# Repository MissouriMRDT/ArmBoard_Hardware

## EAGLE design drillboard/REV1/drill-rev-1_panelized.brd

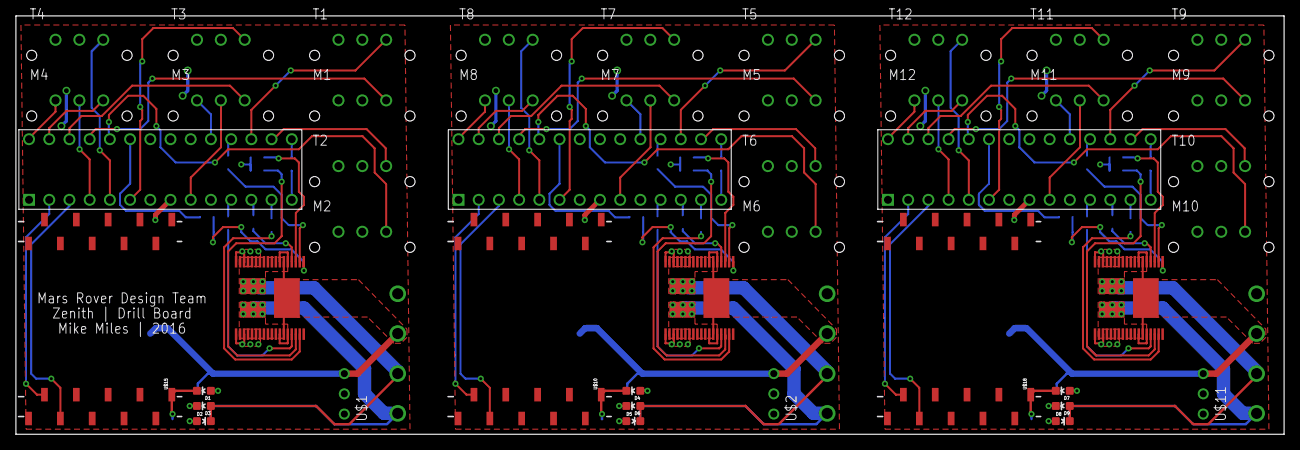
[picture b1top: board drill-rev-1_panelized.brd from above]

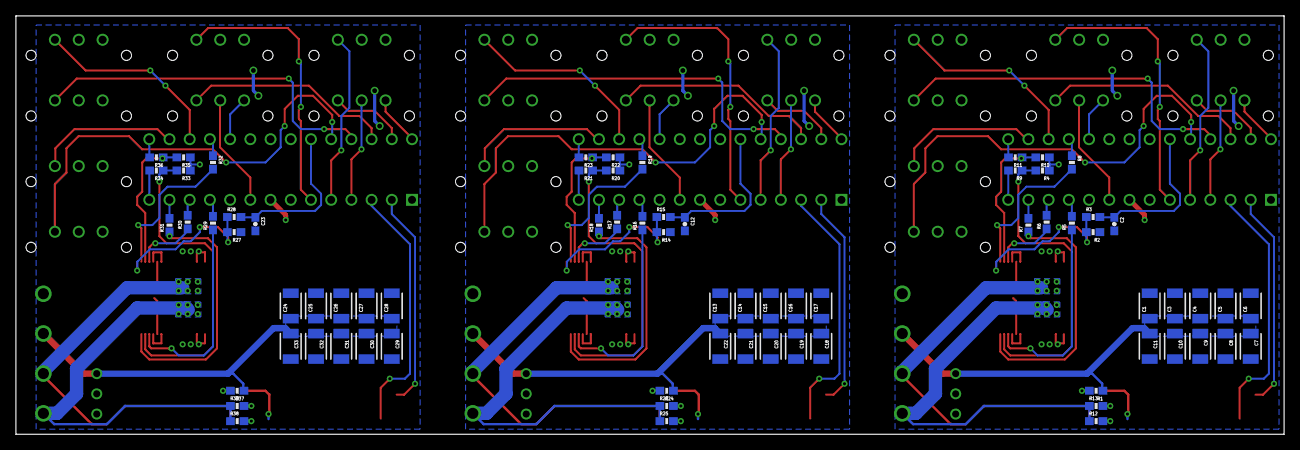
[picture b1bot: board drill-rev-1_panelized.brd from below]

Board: 2 copper layers, 159.4 x 52.6 mm, 123 parts (72 on the bottom side), 108 nets.

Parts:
C1, C3, C4, C5, C6, C7, C8, C9, C10, C11, C13, C14, C15, C16, C17, C18, C19, C20, C21, C22, C24, C25, C26, C27, C28, C29, C30, C31, C32, C33: 47uf; 1210
C2, C12, C23: 33nF; 0603-CAP
D1, D2, D4, D5, D7, D8: red; LED-0603
D3, D6, D9: green; LED-0603
M1, M2, M3, M4, M5, M6, M7, M8, M9, M10, M11, M12: M03VERT; MOLEX0436500328
R1, R5, R6, R7, R9, R11, R12, R13, R16, R17, R18, R21, R23, R24, R25, R26, R29, R30, R31, R34, R36, R37, R38, R39: 1K; 0603-RES
R2, R14, R27: 1.5K; 0603-RES
R3, R15, R28: 10K; 0603-RES
R4, R10, R20, R22, R33, R35: 3K3; 0603-RES
R8, R19, R32: 10k; 0603-RES
T1, T2, T3, T4, T5, T6, T7, T8, T9, T10, T11, T12: M03VERT; MOLEX0436500328
U$1, U$2, U$11: Q_OKI-78SR; OKI-78SR_HORIZ
U$3, U$4, U$5, U$7, U$12, U$14: TE_2POS-5MM_SCREW_TERM
U$6, U$8, U$16: VNH5XXX_HBRIDGEVNH5050A; POWERSSO-36_TP
U$9, U$13, U$17: DIP_SKT_ATMEGA
U$10, U$15, U$18: XBEE_802.15.4SMD; XBEE_802.15.4_SMD

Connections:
+3V1: M5.P$2, M6.P$2, R20.1, R22.1, T5.P$2, T6.P$2, T7.P$2, T8.P$2, U$2.3, U$9.P$7, U$9.P$20, U$9.P$21, U$10.1, U$10.14
+3V2: M9.P$2, M10.P$2, R33.1, R35.1, T9.P$2, T10.P$2, T11.P$2, T12.P$2, U$11.3, U$17.P$7, U$17.P$20, U$17.P$21, U$18.1, U$18.14
+3V3: M1.P$2, M2.P$2, R4.1, R10.1, T1.P$2, T2.P$2, T3.P$2, T4.P$2, U$1.3, U$13.P$7, U$13.P$20, U$13.P$21, U$15.1, U$15.14
+12V: C1.1, C3.1, C4.1, C5.1, C6.1, C7.1, C8.1, C9.1, C10.1, C11.1, R1.1, U$1.1, U$5.P$1, U$6.P$13, U$6.P$24, U$6.SLUG1
+12V1: C13.1, C14.1, C15.1, C16.1, C17.1, C18.1, C19.1, C20.1, C21.1, C22.1, R24.1, U$2.1, U$7.P$1, U$8.P$13, U$8.P$24, U$8.SLUG1
+12V2: C24.1, C25.1, C26.1, C27.1, C28.1, C29.1, C30.1, C31.1, C32.1, C33.1, R37.1, U$11.1, U$14.P$1, U$16.P$13, U$16.P$24, U$16.SLUG1
CS: C2.1, R3.2, U$13.P$23
CS1: C12.1, R15.2, U$9.P$23
CS2: C23.1, R28.2, U$17.P$23
CS_DIS: R8.1, U$13.P$18
CS_DIS1: R19.1, U$9.P$18
CS_DIS2: R32.1, U$17.P$18
D1: M3.P$3, U$13.P$19
D2: M3.P$2, U$13.P$9
D3: M4.P$3, U$13.P$28
D4: M4.P$2, U$13.P$4
D5: M7.P$3, U$9.P$19
D6: M7.P$2, U$9.P$9
D7: M8.P$3, U$9.P$28
D8: M8.P$2, U$9.P$4
D9: M11.P$3, U$17.P$19
D10: M11.P$2, U$17.P$9
D11: M12.P$3, U$17.P$28
D12: M12.P$2, U$17.P$4
ENA: R9.2, U$13.P$14
ENA1: R21.2, U$9.P$14
ENA2: R34.2, U$17.P$14
ENB: R11.2, U$13.P$15
ENB1: R23.2, U$9.P$15
ENB2: R36.2, U$17.P$15
GND: C1.2, C2.2, C3.2, C4.2, C5.2, C6.2, C7.2, C8.2, C9.2, C10.2, C11.2, D1.C, M1.P$3, M2.P$3, R2.1, T1.P$3, T2.P$3, T3.P$3, T4.P$3, U$1.2, U$5.P$2, U$6.P$1, U$6.P$3, U$6.P$4, U$6.P$5, U$6.P$6, U$6.P$7, U$6.P$30, U$6.P$31, U$6.P$32, U$6.P$33, U$6.P$34, U$6.P$36, U$13.P$8, U$13.P$22, U$15.10
GND1: C12.2, C13.2, C14.2, C15.2, C16.2, C17.2, C18.2, C19.2, C20.2, C21.2, C22.2, D4.C, M5.P$3, M6.P$3, R14.1, T5.P$3, T6.P$3, T7.P$3, T8.P$3, U$2.2, U$7.P$2, U$8.P$1, U$8.P$3, U$8.P$4, U$8.P$5, U$8.P$6, U$8.P$7, U$8.P$30, U$8.P$31, U$8.P$32, U$8.P$33, U$8.P$34, U$8.P$36, U$9.P$8, U$9.P$22, U$10.10
GND2: C23.2, C24.2, C25.2, C26.2, C27.2, C28.2, C29.2, C30.2, C31.2, C32.2, C33.2, D7.C, M9.P$3, M10.P$3, R27.1, T9.P$3, T10.P$3, T11.P$3, T12.P$3, U$11.2, U$14.P$2, U$16.P$1, U$16.P$3, U$16.P$4, U$16.P$5, U$16.P$6, U$16.P$7, U$16.P$30, U$16.P$31, U$16.P$32, U$16.P$33, U$16.P$34, U$16.P$36, U$17.P$8, U$17.P$22, U$18.10
INA: R5.2, U$13.P$11
INA1: R16.2, U$9.P$11
INA2: R29.2, U$17.P$11
INB: R6.2, U$13.P$12
INB1: R17.2, U$9.P$12
INB2: R30.2, U$17.P$12
MOIST_1: M1.P$1, U$13.P$25
MOIST_2: M2.P$1, U$13.P$24
MOIST_3: M3.P$1, U$13.P$26
MOIST_4: M4.P$1, U$13.P$27
MOIST_5: M5.P$1, U$9.P$25
MOIST_6: M6.P$1, U$9.P$24
MOIST_7: M7.P$1, U$9.P$26
MOIST_8: M8.P$1, U$9.P$27
MOIST_9: M9.P$1, U$17.P$25
MOIST_10: M10.P$1, U$17.P$24
MOIST_11: M11.P$1, U$17.P$26
MOIST_12: M12.P$1, U$17.P$27
unnamed: R20.2, R21.1, U$8.P$16
unnamed: R4.2, R9.1, U$6.P$16
unnamed: R2.2, R3.1, U$6.P$19
unnamed: D1.A, R1.2
unnamed: D2.A, R12.2
unnamed: R22.2, R23.1, U$8.P$21
unnamed: R10.2, R11.1, U$6.P$21
unnamed: R5.1, U$6.P$15
unnamed: R6.1, U$6.P$22
unnamed: R7.1, U$6.P$17
unnamed: R8.2, U$6.P$20
unnamed: D3.C, R13.2
unnamed: R14.2, R15.1, U$8.P$19
unnamed: R16.1, U$8.P$15
unnamed: R17.1, U$8.P$22
unnamed: R18.1, U$8.P$17
unnamed: R19.2, U$8.P$20
unnamed: D4.A, R24.2
unnamed: D5.A, R25.2
unnamed: D6.C, R26.2
unnamed: R33.2, R34.1, U$16.P$16
unnamed: R35.2, R36.1, U$16.P$21
unnamed: R27.2, R28.1, U$16.P$19
unnamed: R29.1, U$16.P$15
unnamed: R30.1, U$16.P$22
unnamed: R31.1, U$16.P$17
unnamed: R32.2, U$16.P$20
unnamed: D7.A, R37.2
unnamed: D8.A, R38.2
unnamed: D9.C, R39.2
OUTA: R12.1, R13.1, U$3.P$1, U$6.P$2, U$6.P$8, U$6.P$9, U$6.P$10, U$6.P$11, U$6.P$12, U$6.P$14, U$6.SLUG2
OUTA1: R25.1, R26.1, U$4.P$1, U$8.P$2, U$8.P$8, U$8.P$9, U$8.P$10, U$8.P$11, U$8.P$12, U$8.P$14, U$8.SLUG2
OUTA2: R38.1, R39.1, U$12.P$1, U$16.P$2, U$16.P$8, U$16.P$9, U$16.P$10, U$16.P$11, U$16.P$12, U$16.P$14, U$16.SLUG2
OUTB: D2.C, D3.A, U$3.P$2, U$6.P$23, U$6.P$25, U$6.P$26, U$6.P$27, U$6.P$28, U$6.P$29, U$6.P$35, U$6.SLUG3
OUTB1: D5.C, D6.A, U$4.P$2, U$8.P$23, U$8.P$25, U$8.P$26, U$8.P$27, U$8.P$28, U$8.P$29, U$8.P$35, U$8.SLUG3
OUTB2: D8.C, D9.A, U$12.P$2, U$16.P$23, U$16.P$25, U$16.P$26, U$16.P$27, U$16.P$28, U$16.P$29, U$16.P$35, U$16.SLUG3
PWM: R7.2, U$13.P$13
PWM1: R18.2, U$9.P$13
PWM2: R31.2, U$17.P$13
TEMP_1: T1.P$1, U$13.P$17
TEMP_2: T2.P$1, U$13.P$16
TEMP_3: T3.P$1, U$13.P$6
TEMP_4: T4.P$1, U$13.P$5
TEMP_5: T5.P$1, U$9.P$17
TEMP_6: T6.P$1, U$9.P$16
TEMP_7: T7.P$1, U$9.P$6
TEMP_8: T8.P$1, U$9.P$5
TEMP_9: T9.P$1, U$17.P$17
TEMP_10: T10.P$1, U$17.P$16
TEMP_11: T11.P$1, U$17.P$6
TEMP_12: T12.P$1, U$17.P$5
XB_DIN: U$13.P$3, U$15.3
XB_DIN1: U$9.P$3, U$10.3
XB_DIN2: U$17.P$3, U$18.3
XB_DOUT: U$13.P$2, U$15.2
XB_DOUT1: U$9.P$2, U$10.2
XB_DOUT2: U$17.P$2, U$18.2

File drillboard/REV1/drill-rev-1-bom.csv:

"Qty";"Value";"Device";"Package";"Parts";"Description";"";
"1";"1.5K";"RESISTOR0603";"0603-RES";"R2";"Resistor";"";
"1";"10K";"RESISTOR0603";"0603-RES";"R3";"Resistor";"";
"1";"10k";"RESISTOR0603";"0603-RES";"R8";"Resistor";"";
"8";"1K";"RESISTOR0603";"0603-RES";"R1, R5, R6, R7, R9, R11, R12, R13";"Resistor";"";
"1";"33nF";"CAP0603-CAP";"0603-CAP";"C2";"Capacitor";"";
"2";"3K3";"RESISTOR0603";"0603-RES";"R4, R10";"Resistor";"";
"10";"47uf";"CAP1210";"1210";"C1, C3, C4, C5, C6, C7, C8, C9, C10, C11";"Capacitor";"";
"1";"DIP_SKT_ATMEGA";"DIP_SKT_ATMEGA";"DIP_SKT_ATMEGA";"U$13";"";"";
"8";"M03VERT";"M03VERT";"MOLEX0436500328";"M1, M2, M3, M4, T1, T2, T3, T4";"";"";
"1";"Q_OKI-78SR";"Q_OKI-78SR";"OKI-78SR_HORIZ";"U$1";"4.95W DC/DC Converter";"";
"2";"TE_2POS-5MM_SCREW_TERM";"TE_2POS-5MM_SCREW_TERM";"TE_2POS-5MM_SCREW_TERM";"U$3, U$5";"";"";
"1";"VNH5XXX_HBRIDGEVNH5050A";"VNH5XXX_HBRIDGEVNH5050A";"POWERSSO-36_TP";"U$6";"";"";
"1";"XBEE_802.15.4SMD";"XBEE_802.15.4SMD";"XBEE_802.15.4_SMD";"U$15";"";"";
"1";"green";"LED0603";"LED-0603";"D3";"LEDs";"";
"2";"red";"LED0603";"LED-0603";"D1, D2";"LEDs";"";

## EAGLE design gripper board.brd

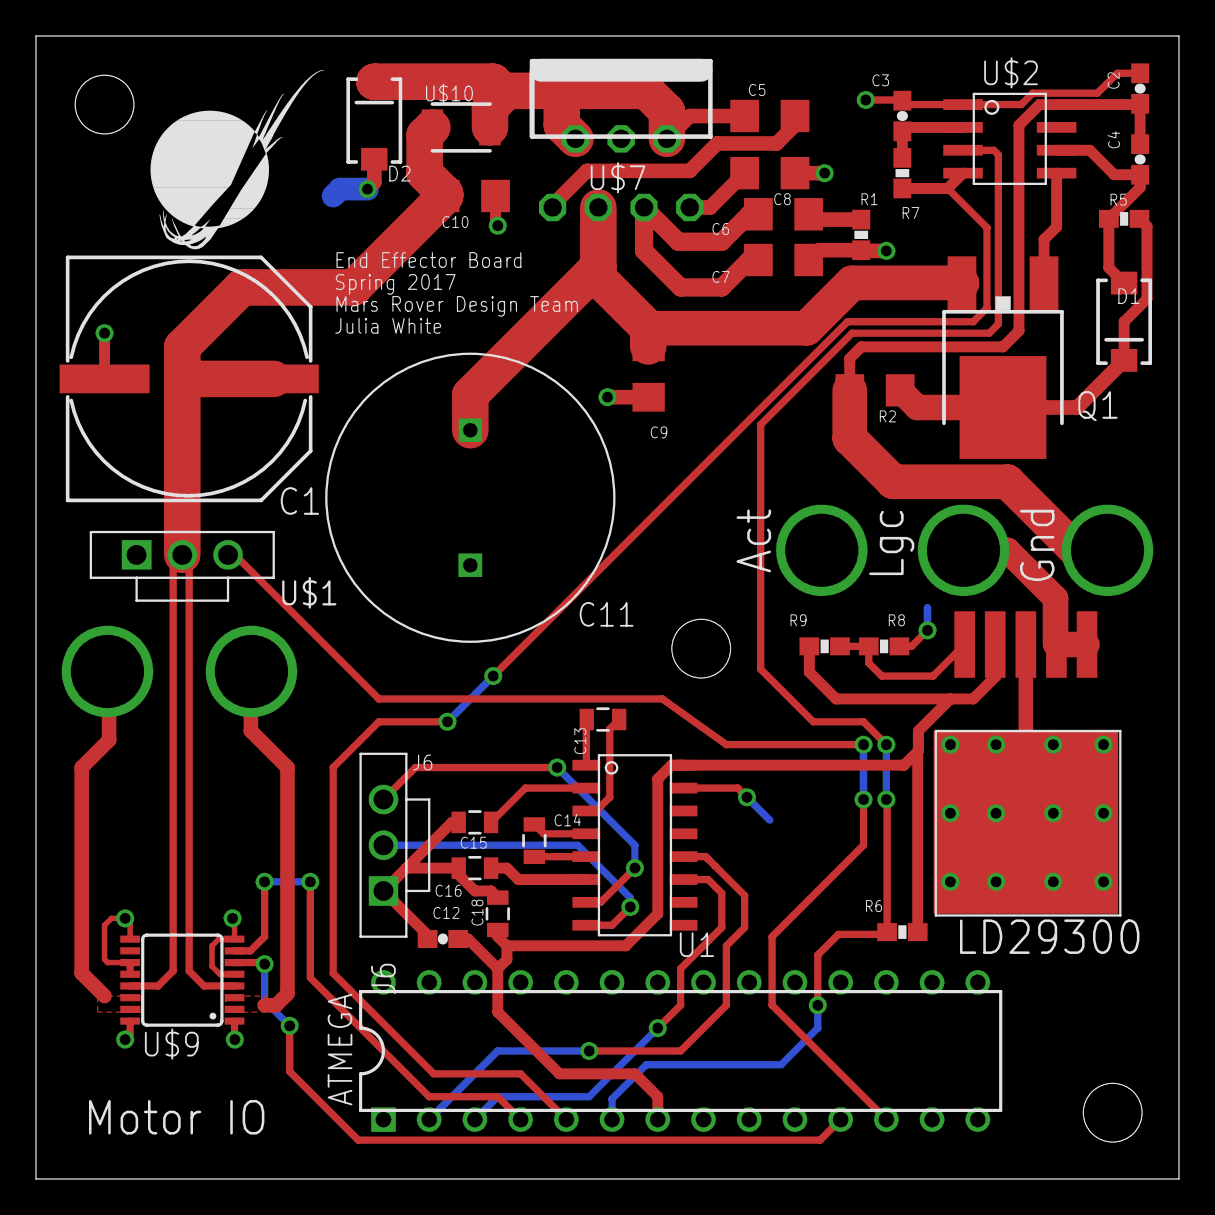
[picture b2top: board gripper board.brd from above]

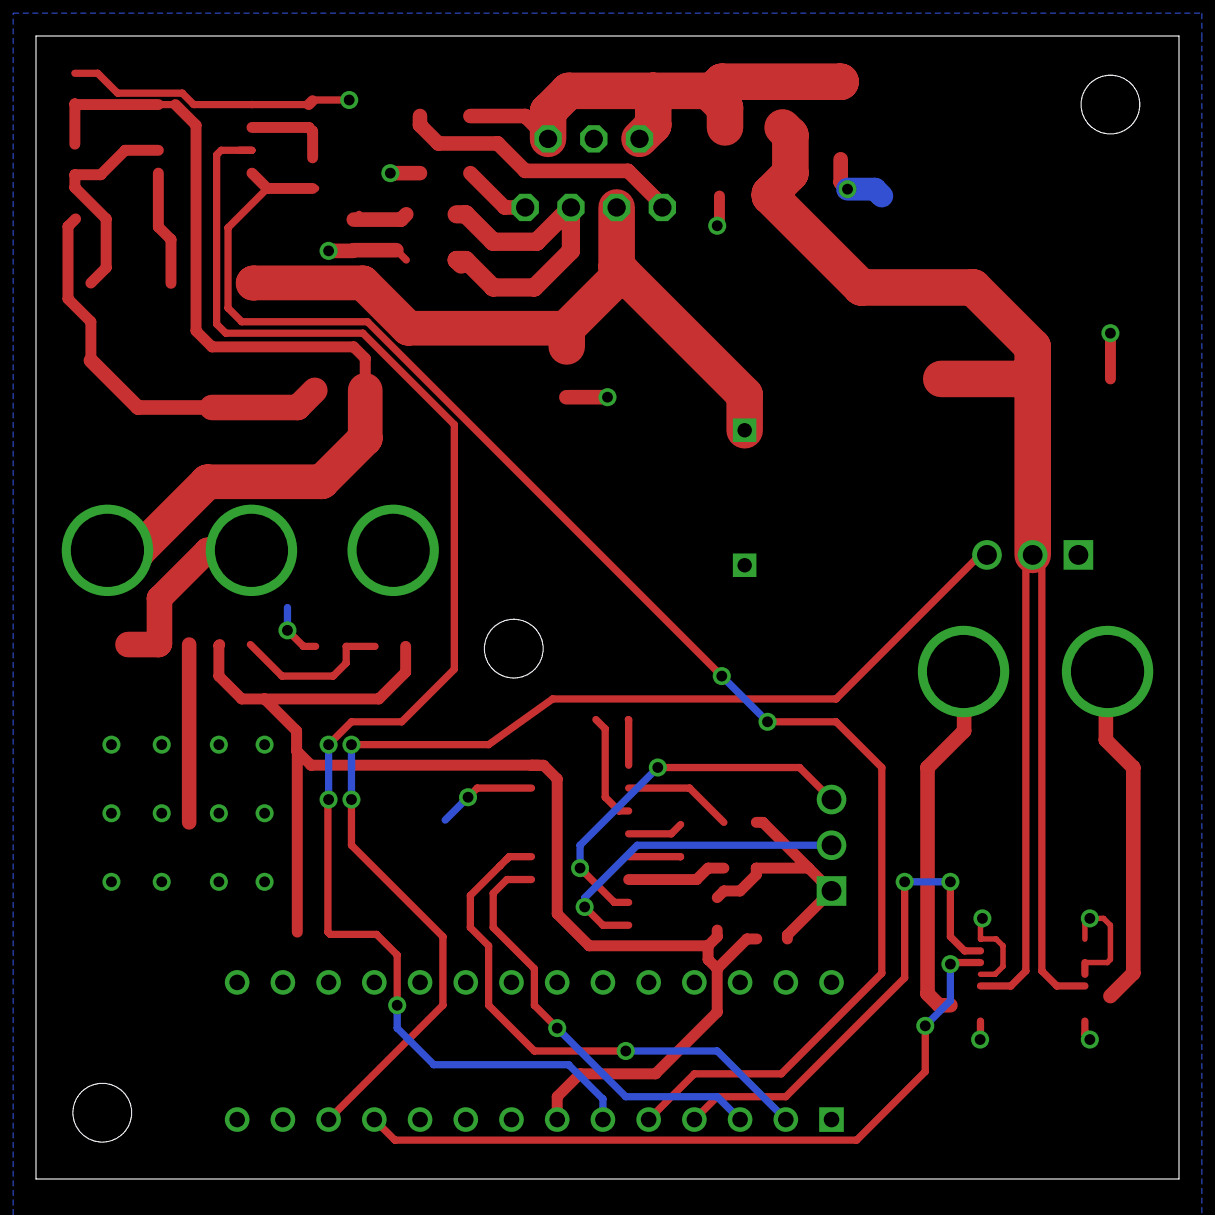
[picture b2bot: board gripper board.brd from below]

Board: 2 copper layers, 63.5 x 63.5 mm, 45 parts (6 on the bottom side), 33 nets.

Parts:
ATMEGA: Q_ATMEGA328P; DIP28
C1: 470uF; PANASONIC_H13
C2: 10uF; 0603-CAP
C3, C4, C12: 1uF; 0603-CAP
C5: .22uF; 1206
C6: 1200pF; 1206
C7: 680pF; 1206
C8, C9, C10: 4.7uF; 1206
C11: 2200uF; C_16MM
C13, C14, C15, C16, C18: .1uF; 0805
D1: SMA-DIODE
D2: DIODE-SCHOTTKY_; SMA-DIODE
H1, H2, H3: MOUNTING_HOLE#4; #4_SCREW
J1, J2, J3, J4, J5: APPPP45_PCB_HORIZ_RIGHT; APP45_PCB_HORIZ_RIGHT
J6: SL03; MOLEX-70543-0002
LOGO1: MRDT_LOGO
Q1: MOSFET-NCHANNELFDD8780; DPAK
R1, R6: 5100 ohm; 0603-RES
R2: .01; 1206
R5: 10000 ohm; 0603-RES
R7: 2000 ohm; 0603-RES
R8: 1000 ohm; 0603-RES
R9: 3000 ohm; 0603-RES
U1: MAX232D; SOIC16
U$1: SERVOMOLEX_SL_VERT_TH; MOLEX-70543-0002
U$2: LT1910; SOIC8
U$7: SI-8050Y; TO-220-7
U$8: LD29300; P2PAK
U$9: MAX14871; TSSOP-16
U$10: 56UH; 1210

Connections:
5VIN: ATMEGA.7, C12.2, C18.1, R6.2, R9.1, U1.16, U$8.4
5VMTR: C1.+, C10.2, U$1.2, U$9.4, U$9.13, U$10.2
12VLGC: J2.P$1, U$8.1, U$8.2
12VMTR: C9.2, C11.+, Q1.3, U$7.3
ACTPWR: C2.2, C4.2, J3.P$1, R2.2, U$2.8
ATMEGA2MAX: ATMEGA.3, U1.11
FAULT: ATMEGA.6, R6.1, U$2.3
GND: ATMEGA.8, ATMEGA.22, C1.-, C2.1, C3.2, C7.1, C8.1, C9.1, C10.1, C11.GND, C12.1, C15.2, C16.2, C18.2, D2.A, J1.P$1, J6.1, R1.1, R8.2, U1.15, U$1.1, U$2.1, U$7.4, U$8.3, U$8.P$1, U$9.1, U$9.5, U$9.8, U$9.9, U$9.11, U$9.12, U$9.16
MAX2ATMEGA: ATMEGA.2, U1.12
MICROCNTRL: ATMEGA.5, R7.1, U$2.4
MTR1_1: J4.P$1, U$9.2, U$9.3
MTR1_2: J5.P$1, U$9.14, U$9.15
MTR1_DIR: ATMEGA.4, U$9.7
MTR1_PWM: ATMEGA.11, U$9.6
unnamed: C3.1, R7.2, U$2.2
unnamed: R8.1, R9.2, U$8.5
unnamed: C13.2, U1.3
unnamed: C6.1, R1.2
unnamed: C4.1, D1.A, R5.1, U$2.6
unnamed: Q1.1, U$2.5
unnamed: C8.2, U$7.7
unnamed: D1.C, Q1.4, R2.1, R5.2
unnamed: C6.2, C7.2, U$7.5
unnamed: C5.2, U$7.1
unnamed: C14.2, U1.5
unnamed: C14.1, U1.4
unnamed: C13.1, U1.1
unnamed: C15.1, U1.2
unnamed: C16.1, U1.6
unnamed: J6.3, U1.7
unnamed: J6.2, U1.8
unnamed: C5.1, D2.C, U$7.2, U$7.6, U$10.1
SERVOIN: ATMEGA.12, U$1.3

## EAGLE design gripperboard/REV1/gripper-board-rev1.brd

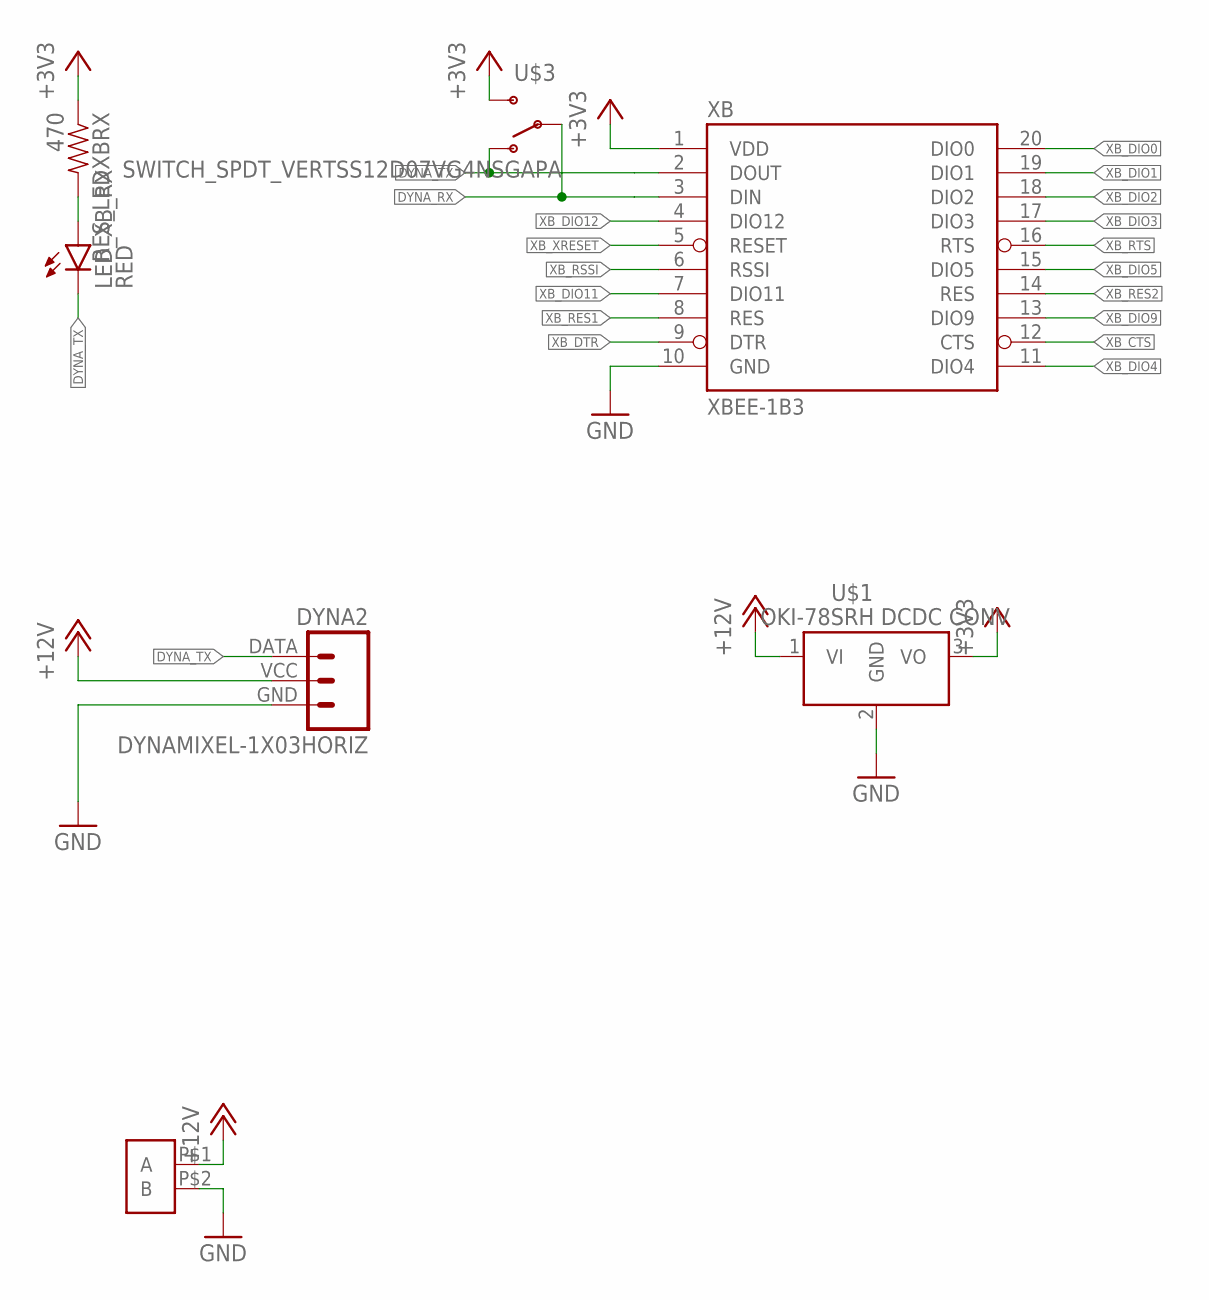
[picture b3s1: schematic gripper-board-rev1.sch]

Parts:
DYNA2: DYNAMIXEL-1X03HORIZ; MLX-SPOX5268-3PIN
LED_XB_RX: RED; LED-1206
RES_LEDXBRX: 470; 1206
U$1: Q_OKI-78SR; OKI-78SR_HORIZ
U$2: 2POS_TERM_BLOCKPHOENIX-1935161; PHOENIX-1935161
U$3: SWITCH_SPDT_VERTSS12D07VG4NSGAPA; C&K-SS12D07VG4NSGAPA
XB: XBEE-1B3; XBEE-SMD

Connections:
+3V3: RES_LEDXBRX.1, U$1.3 (VO), U$3.P$3 (S), XB.1 (VDD)
+12V: DYNA2.VCC, U$1.1 (VI), U$2.P$1 (A)
DYNA_RX: U$3.P$2, XB.3 (DIN)
DYNA_TX: DYNA2.DATA, LED_XB_RX.C, U$3.P$1 (O), XB.2 (DOUT)
GND: DYNA2.GND, U$1.2 (GND), U$2.P$2 (B), XB.10 (GND)
unnamed: LED_XB_RX.A, RES_LEDXBRX.2
XB_CTS: XB.12 (CTS)
XB_DIO0: XB.20 (DIO0)
XB_DIO1: XB.19 (DIO1)
XB_DIO2: XB.18 (DIO2)
XB_DIO3: XB.17 (DIO3)
XB_DIO4: XB.11 (DIO4)
XB_DIO5: XB.15 (DIO5)
XB_DIO9: XB.13 (DIO9)
XB_DIO11: XB.7 (DIO11)
XB_DIO12: XB.4 (DIO12)
XB_DTR: XB.9 (DTR)
XB_RES1: XB.8 (RES)
XB_RES2: XB.14 (RES)
XB_RSSI: XB.6 (RSSI)
XB_RTS: XB.16 (RTS)
XB_XRESET: XB.5 (RESET)

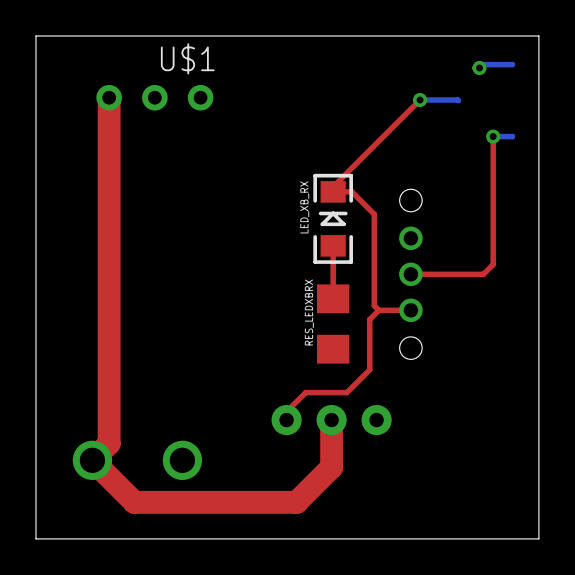
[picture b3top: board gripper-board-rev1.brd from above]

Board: 2 copper layers, 27.9 x 27.9 mm, 7 parts (1 on the bottom side), 6 nets.

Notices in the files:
parts and their libraries:
SparkFun-Resistors: Licensing: Creative Commons ShareAlike 4.0 International - https://creativecommons.org/licenses/by-sa/4.0
SparkFun-Capacitors: Licensing: CC v3.0 Share-Alike You are welcome to use this library for commercial purposes.
